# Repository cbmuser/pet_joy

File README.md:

# pet_joy

CBM Pet Joystick, Wifi and CB2-Sound

Stupid PET Tricks Single and Dual-Joystick (supports Auto-Fire-Joystick)

Wifi-Modem @2400 Baud (and less) with NTP-Time

CB2-Sound with gain-stage

Wifi- and Joystick-Mode switchable by one jumper

The adapter is connected to the Userport and uses the 8 bit I/Os and the handshake-line for the additional hardware. There are three joystick-ports, a dual-joystick and the "Stupid PET Tricks"-port. The ports, also CB2 used for 1bit-Sound are switchable to the Wifi-modem by a 74LS257 Multiplexer and a jumper. 
It uses the known, modded C64 Wifi-Modem software and a Wemos D1 Mini. It was tested with the second PET board 2001N and a CBM 8296. For the CB2-line a seperate jumper is included to disconnect the LM386 amplifier, because in Wifi-mode it will produce aggy Rx-responses on the audio-line.

>[!CAUTION]
>Use it on your own risc ! - This is open hard- and software.

## Update-Diary
4.8.2025
The again modded firmware for the Wemos D1 Mini was added. It uses like the PETTERM a 2400 Baud lauch. If you want to request and display NTP-time, you can set your timezone "at$tiz=2" for UTC+2. Write this to your setup "at&w" and after connecting to Wifi you can display date and time "at$t".

>[!IMPORTANT]
The C2N Power- and Breakout-Adapter Gerbers were exchanged. The USB-Pinout was wrong, but it's easy to fix. 
````
Look from the back-side to the pins:
GND
B9
A5
B5
A9
GND

Solder the pins:B9 to A5 and B5 to A9. 

````
Sorry for that, it was done in a hurry. 

17.7.25
Added the PETTERM v0.7.0 using the 2400 Baud fix. If it won't work and you struggeling with messy chars, pick up the original release and give it a try. You can adjust the timing in petterm.s, line 618.

15.7.25
The "2400 Baud"-Issue is nearly fixed. The PETTERM bitbanging IRQ lo-timer must be adjusted to the seemingly a touch faster WEMOS D1 Mini. It's in testing and an updated PETTERM for this setup will follow soon.

13.7.25
Two adapters: the "horizontal Joystick" and a "C2N-Breakout and Power-Adapter" were added in the adapter-folder. In the ZIPs you'll find Gerber production data.

## Joystick-Ports

<code>
Dual-Joystick
[PA0] UP     ---> Fire
[PA1] DOWN   ---> Fire
[PA2] LEFT
[PA3] RIGHT
[PA4] UP    ---> Fire 
[PA5] DOWN  ---> Fire
[PA6] LEFT
[PA7] RIGHT
Fire (Sub-D Pin 6) is coupled by two ports and two 4148 diodes. 

Stupid PET Tricks (Single Joystick)
[PA0] LEFT
[PA1] RIGHT
[PA2] UP
[PA3] DOWN
[PA4] UNUSED
[PA5] FIRE
[PA6] UNUSED
[PA7] UNUSED
</code>

## CB2-Sound
For driving and decoupling the CB2-Sound a LM386 driver is included. You can adjust the volume by the 10K potentiometer. It is only a small gain-stage (max. x20) to drive a 1 Watt/8Ohm speaker.

## WIFI-Modem
With the Wifi-Modem you'll able to connect your PET to a BBS by Telnet and the PETTERM. It uses the known, modded firmware for the WEMOS D1 NodeMCU. 

## PCB

With the JOY/WIFI-Jumper you can swich between Joystick (open) oder Wifi (closed). With the Jumper near the LM386 you can cut the audio-line. On the right, below Joystick#1-port you can connect a small speaker. 

### Parts

#### Bottom

8x BSS138 (SOT-23)

8x 330 Ohm (0805)

10x 10K (0805)

1x Pullup, something between 1,5-2K2 (0805)

#### Top

74LS257 THT/DIP

1x Ceramic Capacitor 100nF THT

4x 4148 DIP

2x 100µF Elko

1x Piher PT6 10K

USB-C 6pol (USB4125-GF-A-0190), JST-connector (+5V round, GND square) or soldered wires for +5V and GND

>[!CAUTION]
>The supply must be 5V+ ! 

2 Jumper and three Pin-headers 2pol

1x Wemos D1 Mini NodeMCU

1x LM386 Audio Amp

2x Sub-D 9pol horizontal, male (print)

1x Sub-D 9pol vertical,male (print)

1x Userport-Connector

## Links

Firmware: http://www.mediafire.com/file/tm71a1oa1a3macc/alwyz_modded_firmware.rar

PETTERM: https://github.com/ChartreuseK/PETTERM

### Games
Old: https://archive.org/details/softwarelibrary_pet or https://portcommodore.com/files/petfiles.htm

New: https://itch.io/games/tag-commodore-pet

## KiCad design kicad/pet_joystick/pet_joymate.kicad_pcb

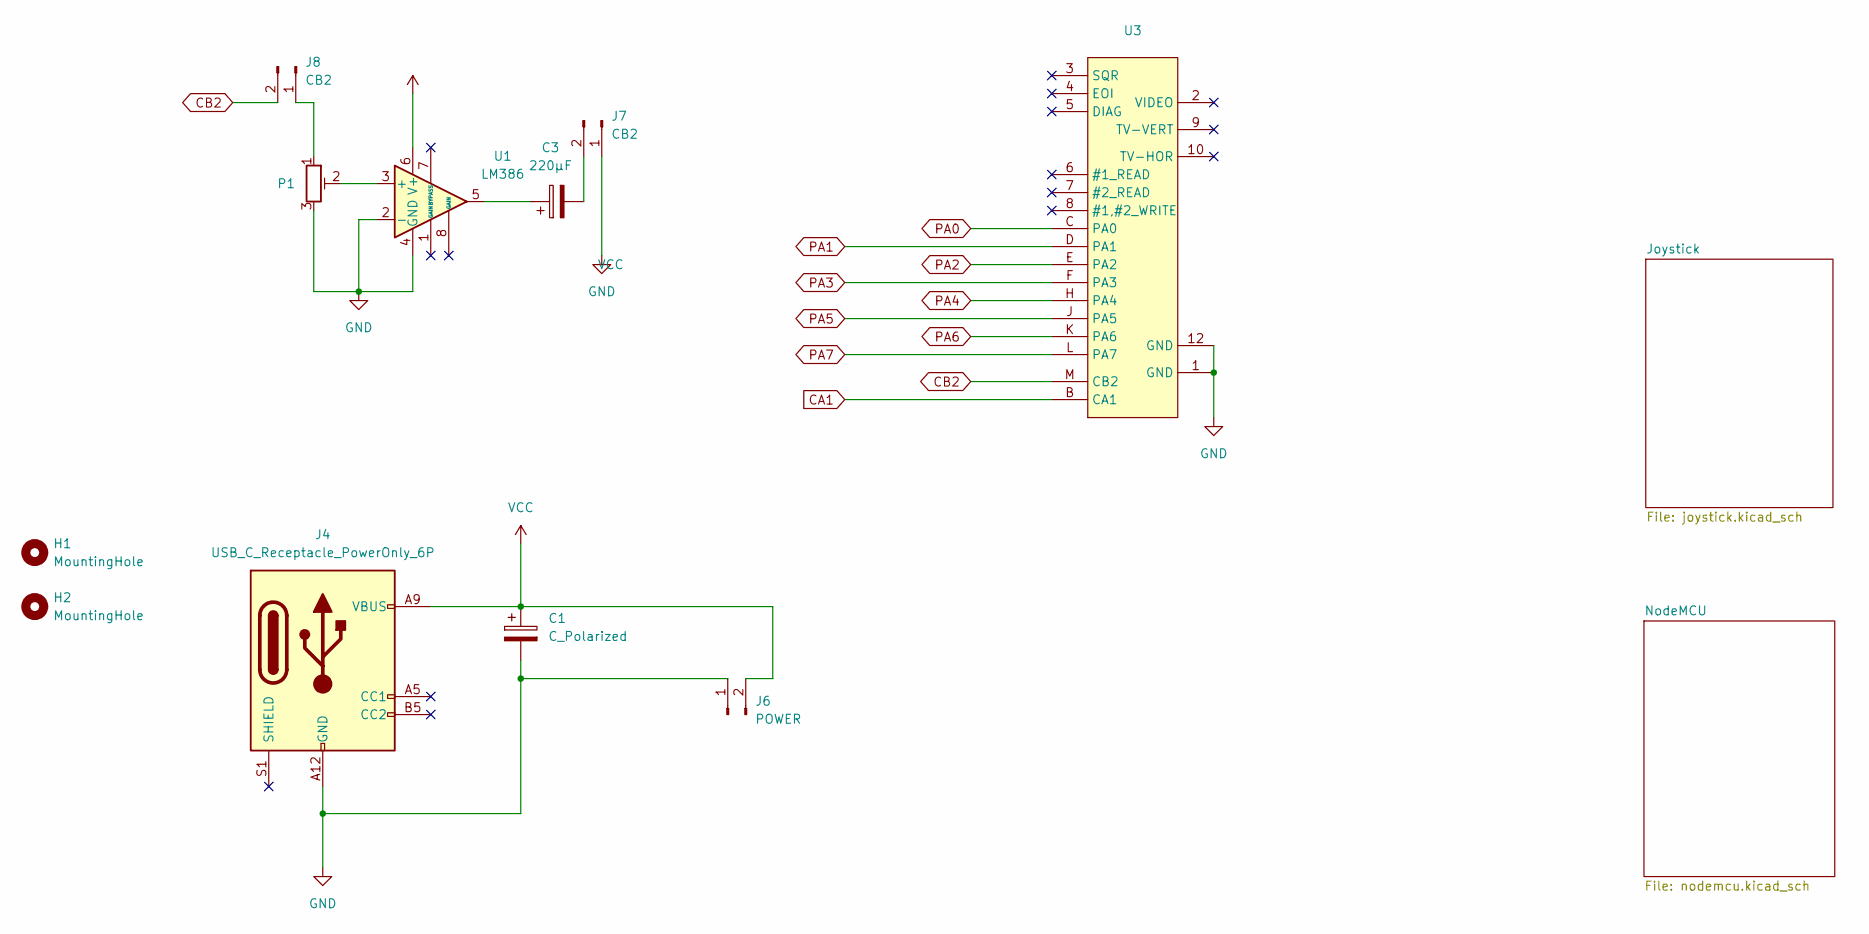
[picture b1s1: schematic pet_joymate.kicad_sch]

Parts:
C1: C_Polarized; CP_Radial_D8.0mm_P2.50mm
C3: 220µF; CP_Radial_D8.0mm_P2.50mm
H1, H2: MountingHole; MountingHole_3.2mm_M3
J4: USB_C_Receptacle_PowerOnly_6P; USB_C_Receptacle_HRO_TYPE-C-31-M-17
J6: POWER; JST_XA_B02B-XASK-1-A_1x02_P2.50mm_Vertical
J7: CB2; PinHeader_1x02_P2.54mm_Vertical
J8: CB2; PinSocket_1x02_P2.54mm_Vertical
P1: R_Potentiometer_Trim; Potentiometer_Piher_PT-6-H_Horizontal
U1: LM386; DIP-8_W7.62mm
U3: C64-User-Port-Female

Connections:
CA1: U3.B (CA1); also elsewhere on the board
CB2: J8.2, U3.M (CB2); also elsewhere on the board
GND: C1.2, J4.A12 (GND), J4.B12 (GND), J6.1, J7.1, P1.3, U1.2 (-), U1.4 (GND), U3.1 (GND), U3.12 (GND); also elsewhere on the board
unnamed: C3.1, U1.5
unnamed: C3.2, J7.2
unnamed: J8.1, P1.1
unnamed: P1.2, U1.3 (+)
PA0: U3.C (PA0); also elsewhere on the board
PA1: U3.D (PA1); also elsewhere on the board
PA2: U3.E (PA2); also elsewhere on the board
PA3: U3.F (PA3); also elsewhere on the board
PA4: U3.H (PA4); also elsewhere on the board
PA5: U3.J (PA5); also elsewhere on the board
PA6: U3.K (PA6); also elsewhere on the board
PA7: U3.L (PA7); also elsewhere on the board
VCC: C1.1, J4.A9 (VBUS), J4.B9 (VBUS), J6.2, U1.6 (V+); also elsewhere on the board

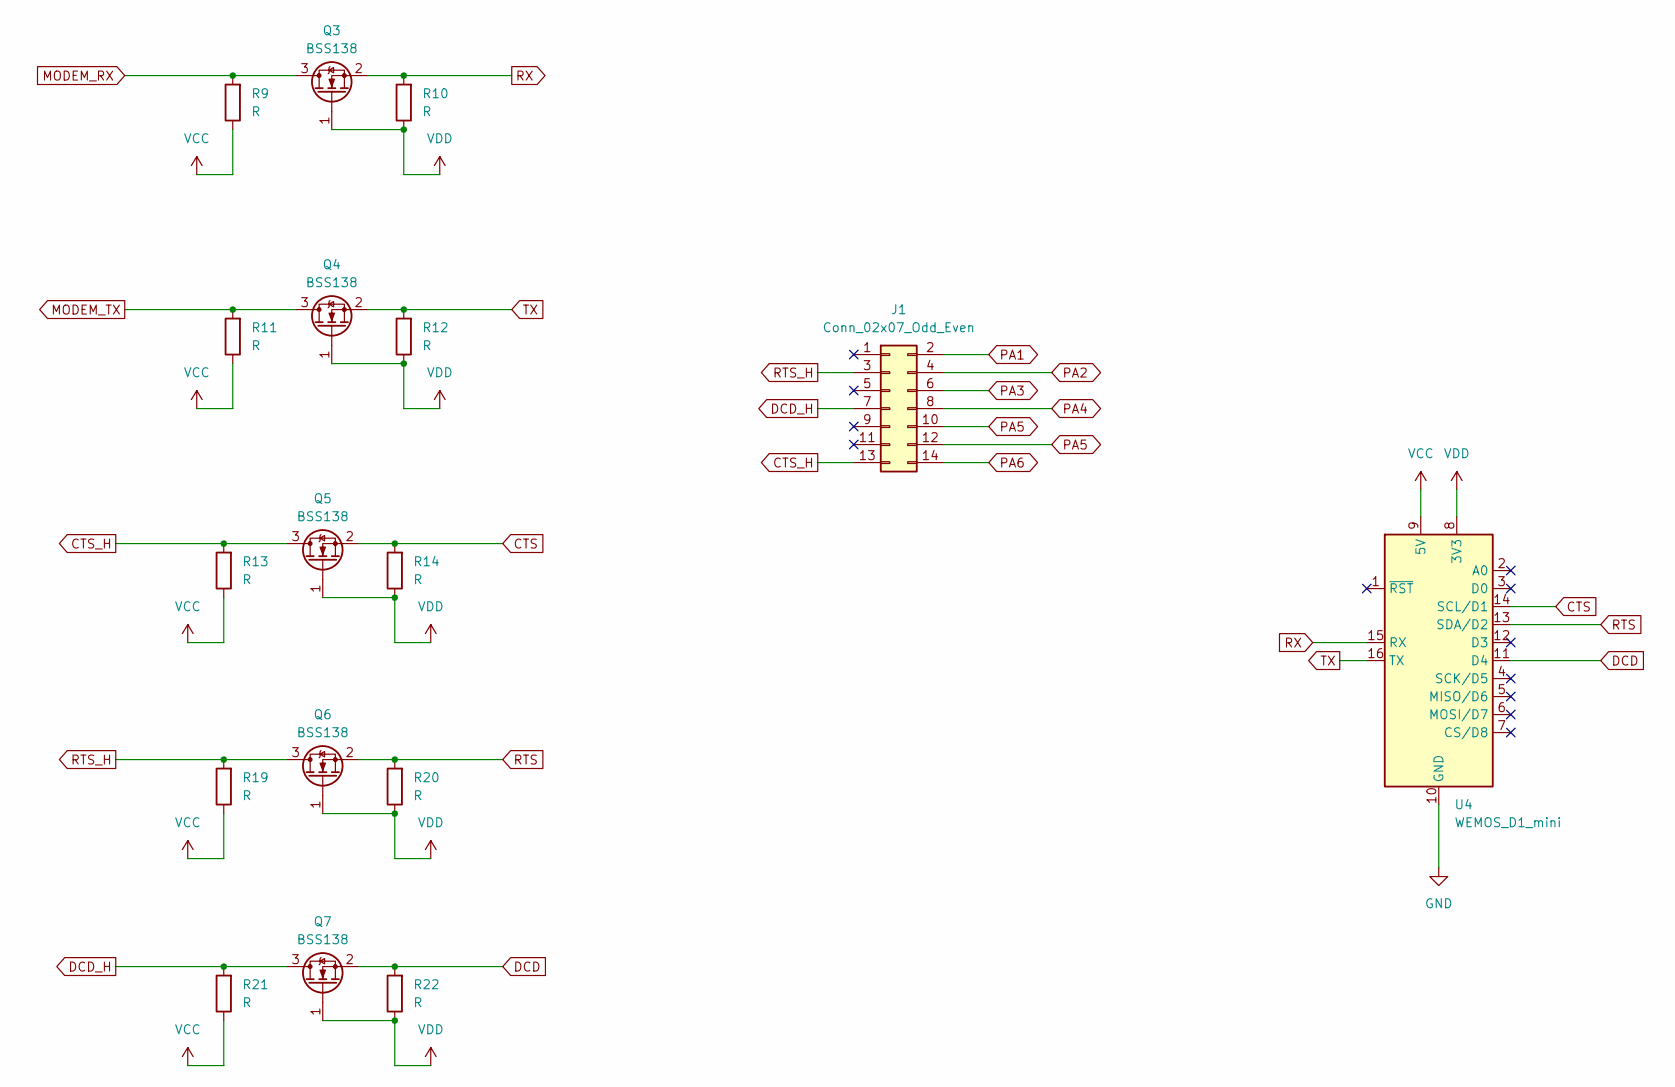
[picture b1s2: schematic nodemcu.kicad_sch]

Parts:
J1: Conn_02x07_Odd_Even; PinHeader_2x07_P2.54mm_Vertical
Q3, Q4, Q5, Q6, Q7: BSS138; SOT-23
R9, R10, R11, R12, R13, R14, R19, R20, R21, R22: R; R_0805_2012Metric
U4: WEMOS_D1_mini; WEMOS_D1_mini_light

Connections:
CTS: Q5.2 (S), R14.2, U4.14 (SCL/D1)
CTS_H: J1.13, Q5.3 (D), R13.2
DCD: Q7.2 (S), R22.2, U4.11 (D4)
DCD_H: J1.7, Q7.3 (D), R21.2
GND: U4.10 (GND); also elsewhere on the board
MODEM_RX: Q3.3 (D), R9.2; also elsewhere on the board
MODEM_TX: Q4.3 (D), R11.2; also elsewhere on the board
PA1: J1.2; also elsewhere on the board
PA2: J1.4; also elsewhere on the board
PA3: J1.6; also elsewhere on the board
PA4: J1.8; also elsewhere on the board
PA5: J1.10, J1.12; also elsewhere on the board
PA6: J1.14; also elsewhere on the board
RTS: Q6.2 (S), R20.2, U4.13 (SDA/D2)
RTS_H: J1.3, Q6.3 (D), R19.2
RX: Q3.2 (S), R10.2, U4.15 (RX)
TX: Q4.2 (S), R12.2, U4.16 (TX)
VCC: R9.1, R11.1, R13.1, R19.1, R21.1, U4.9 (5V); also elsewhere on the board
VDD: Q3.1 (G), Q4.1 (G), Q5.1 (G), Q6.1 (G), Q7.1 (G), R10.1, R12.1, R14.1, R20.1, R22.1, U4.8 (3V3)

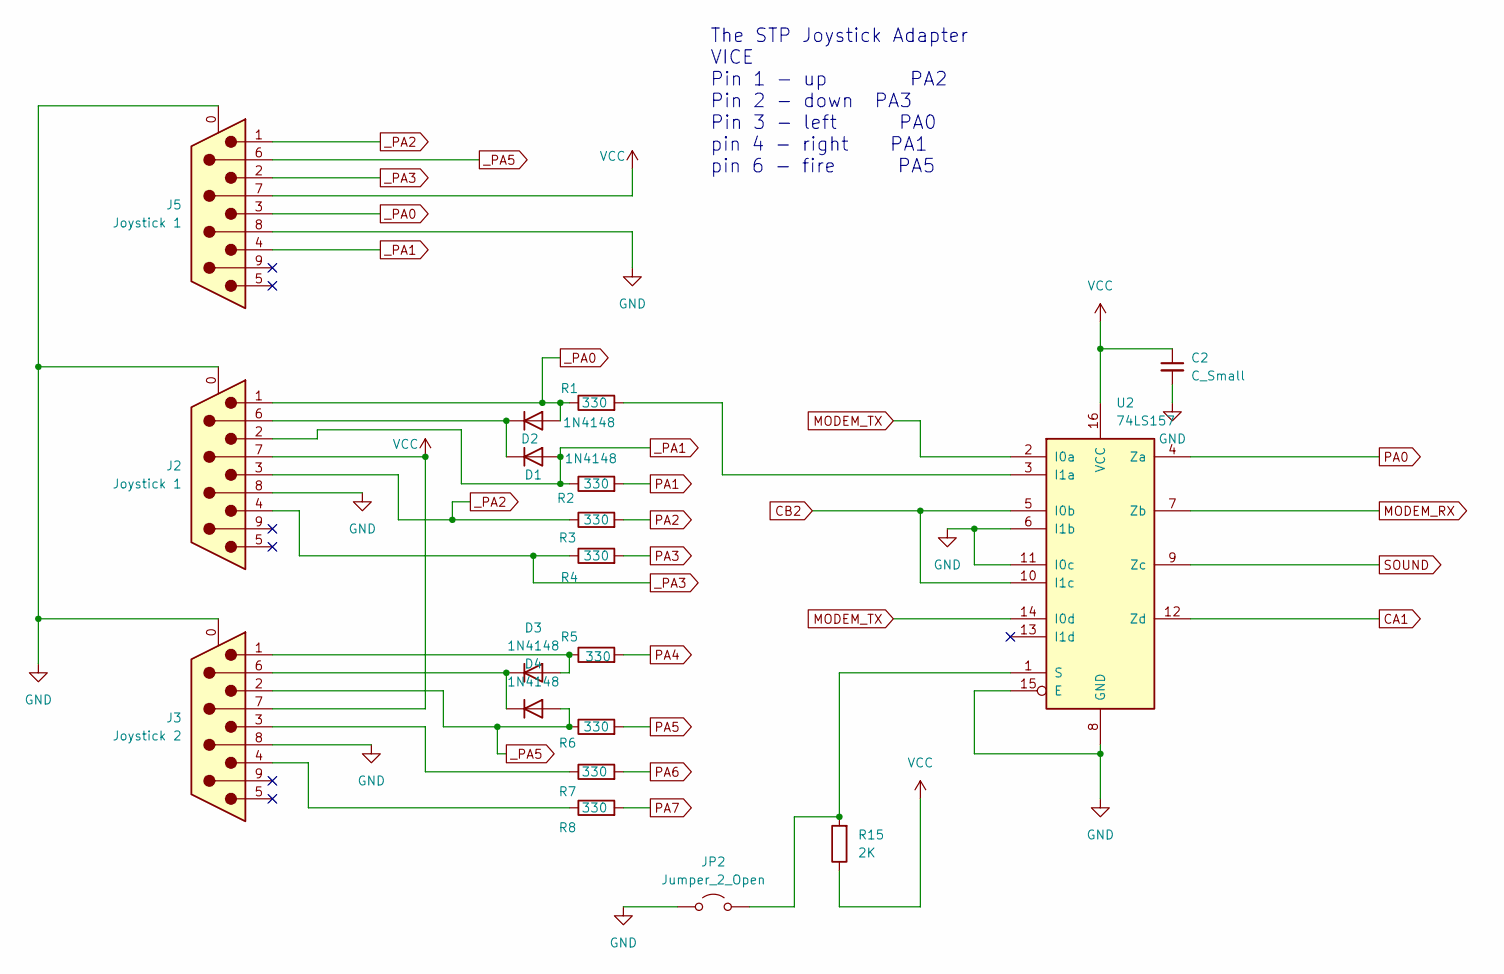
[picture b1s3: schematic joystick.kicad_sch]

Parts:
C2: C_Small; C_Disc_D3.0mm_W1.6mm_P2.50mm
D1, D2, D3, D4: 1N4148; D_DO-35_SOD27_P7.62mm_Horizontal
J2: Joystick 1; DSUB-9_Male_Horizontal_P2.77x2.84mm_EdgePinOffset4.94mm_Hou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
J3: Joystick 2; DSUB-9_Male_Horizontal_P2.77x2.84mm_EdgePinOffset4.94mm_Hou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
J5: Joystick 1; DSUB-9_Female_Vertical_P2.77x2.84mm_MountingHoles
JP2: Jumper_2_Open; TestPoint_2Pads_Pitch2.54mm_Drill0.8mm
R1, R2, R3, R4, R5, R6, R7, R8: 330; R_0805_2012Metric
R15: 2K; R_0805_2012Metric
U2: 74LS157; DIP-16_W7.62mm

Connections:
CA1: U2.12 (Zd); also elsewhere on the board
CB2: U2.5 (I0b), U2.10 (I1c); also elsewhere on the board
GND: C2.2, J2.0 (PAD), J2.8, J3.0 (PAD), J3.8, J5.0 (PAD), J5.8, JP2.1 (A), U2.6 (I1b), U2.8 (GND), U2.11 (I0c), U2.15 (E); also elsewhere on the board
MODEM_RX: U2.7 (Zb); also elsewhere on the board
MODEM_TX: U2.2 (I0a), U2.14 (I0d); also elsewhere on the board
unnamed: D1.1 (K), D2.1 (K), J2.6
unnamed: D3.2 (A), J3.1, R5.1
unnamed: D3.1 (K), D4.1 (K), J3.6
unnamed: J3.3, R7.1
unnamed: J3.4, R8.1
unnamed: JP2.2 (B), R15.2, U2.1 (S)
unnamed: R1.2, U2.3 (I1a)
PA0: U2.4 (Za); also elsewhere on the board
PA1: R2.2; also elsewhere on the board
PA2: R3.2; also elsewhere on the board
PA3: R4.2; also elsewhere on the board
PA4: R5.2; also elsewhere on the board
PA5: R6.2; also elsewhere on the board
PA6: R7.2; also elsewhere on the board
PA7: R8.2; also elsewhere on the board
SOUND: U2.9 (Zc)
VCC: C2.1, J2.7, J3.7, J5.7, R15.1, U2.16 (VCC); also elsewhere on the board
_PA0: D2.2 (A), J2.1, J5.3, R1.1
_PA1: D1.2 (A), J2.2, J5.4, R2.1
_PA2: J2.3, J5.1, R3.1
_PA3: J2.4, J5.2, R4.1
_PA5: D4.2 (A), J3.2, J5.6, R6.1

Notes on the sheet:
The STP Joystick Adapter VICE Pin 1 - up PA2 Pin 2 - down PA3 Pin 3 - left PA0 pin 4 - right PA1 pin 6 - fire PA5

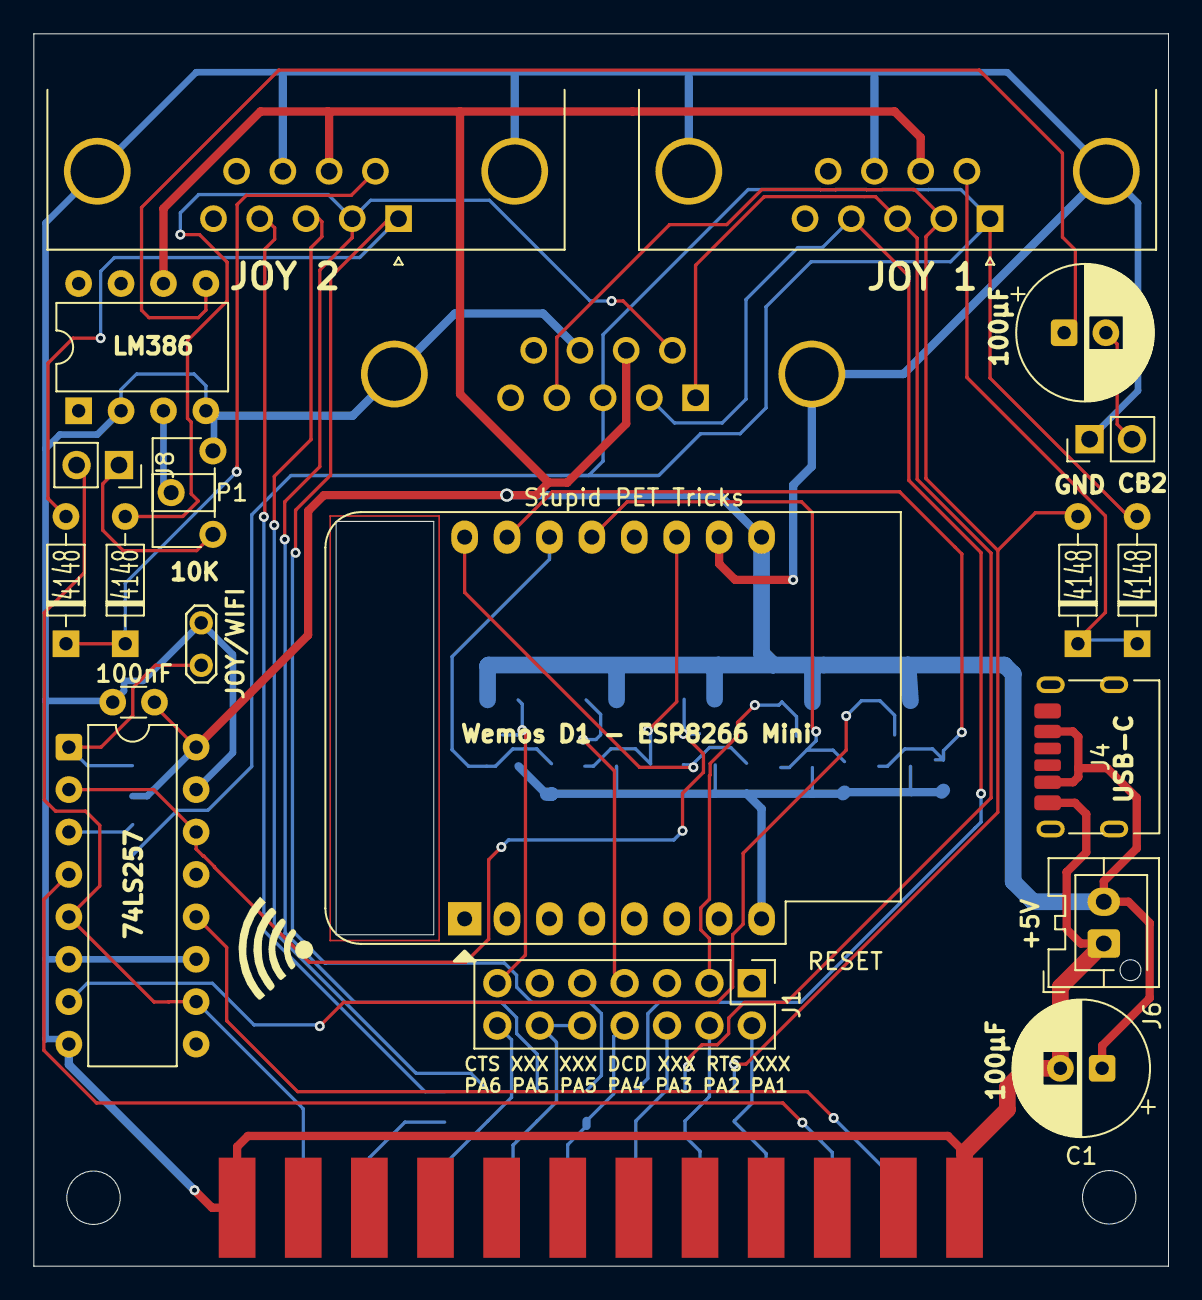
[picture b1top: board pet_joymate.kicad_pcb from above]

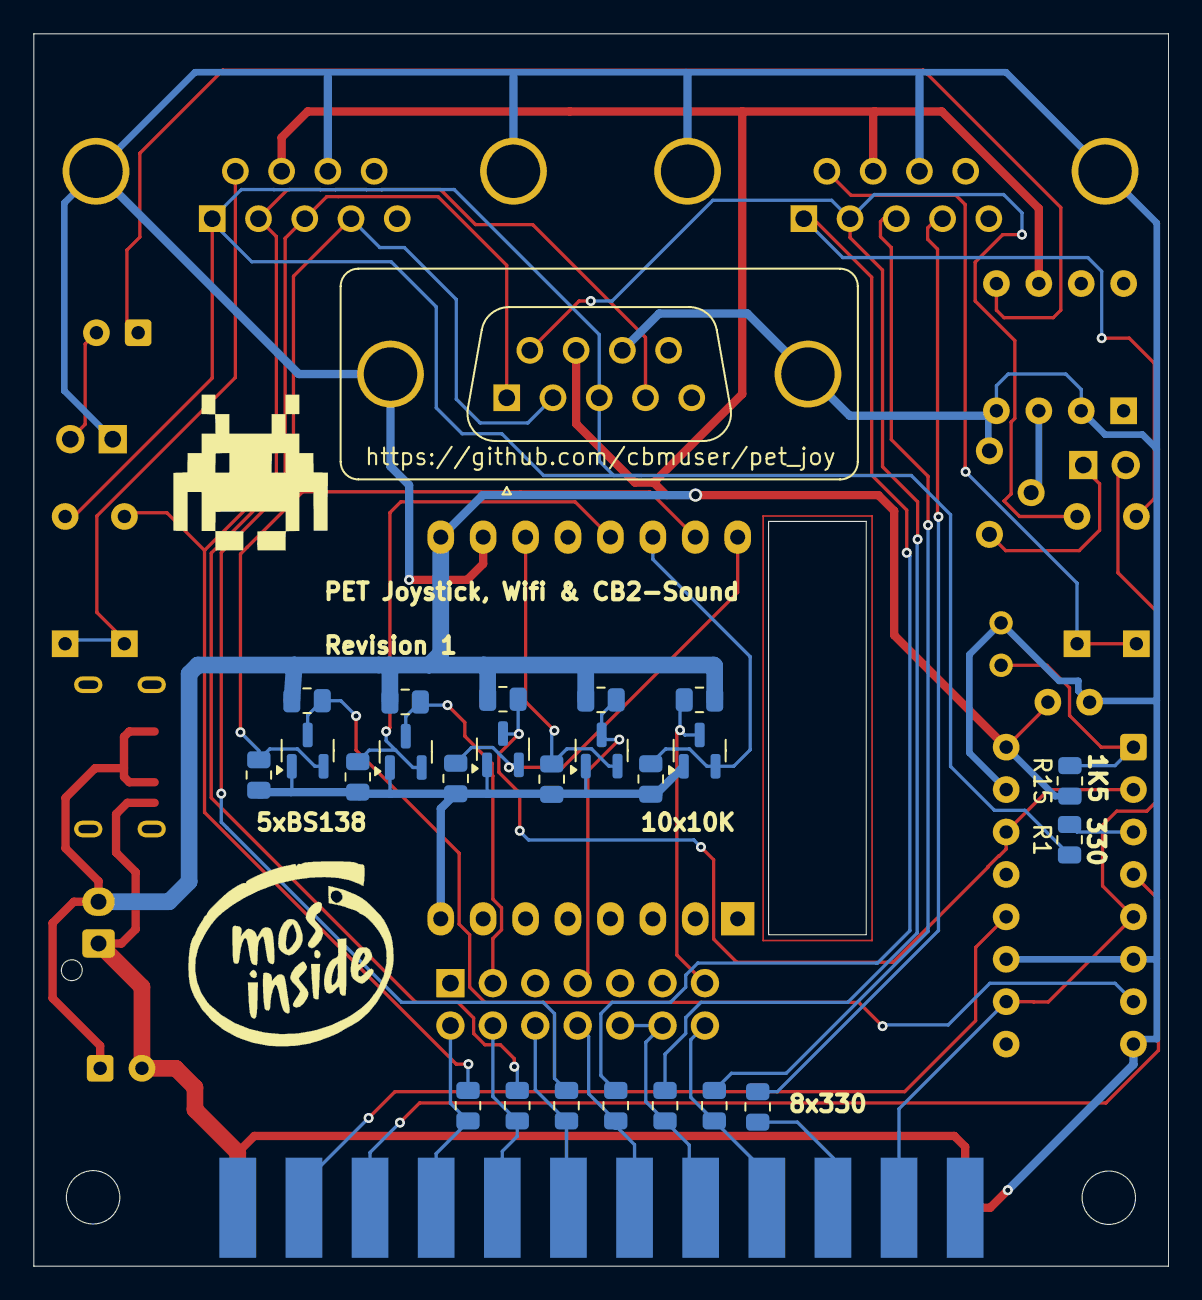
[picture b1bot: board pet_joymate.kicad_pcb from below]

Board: 2 copper layers, 67.9 x 73.8 mm, 47 parts (25 on the bottom side), 39 nets.

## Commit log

2025-07-06 KiCad and Gerber
2025-07-06 Games for the Dual-Joystickport
2025-07-06 images
2025-07-07 Delete images/pcb.png
    minor change
2025-07-07 Images
    minor change in silkscreen
2025-07-07 Kicad and Gerber
    typo in silkscreen: bs138 to bss138
2025-07-13 C2N Breakout and RS232 horizontal
2025-07-13 Gerber
    C2N-Breakout and RS232 horizontal
2025-07-13 KiCad and Gerber
    Revision 1a
2025-07-15 CBM 8296 and PETTERM
2025-07-15 Adapters
2025-07-15 Adapter for horizontal Joystick-Port
2025-07-15 C2N-Breakout and Power
2025-07-15 C2N Breakout and Power - Gerber
2025-07-15 Joystick-Adapter horizontal - Gerber
2025-07-15 add diary
2025-07-15 Adapter for horizontal Joystick-Assembly
2025-07-17 PETTERM 0.7.0
    [G]raphic and [B]usiness Versions of the PETTERM using a 2400 Baud Fix
2025-07-17 See Update-Diary
2025-08-04 Delete adapter/c2npower.zip
    USB Pinout wrong
2025-08-04 C2N Breakout and Power
    Fixed USB-Pinout
2025-08-04 Wemos D1 Mini Firmware (2400 Baud launch)
